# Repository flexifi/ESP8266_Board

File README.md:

# ESP8266_Board
A USB2Wifi test board to help working with and testing ESP8266 AT Commands.

(C)2015 Radu Motisan
http://www.pocketmagic.net/esp8266-troubleshooting

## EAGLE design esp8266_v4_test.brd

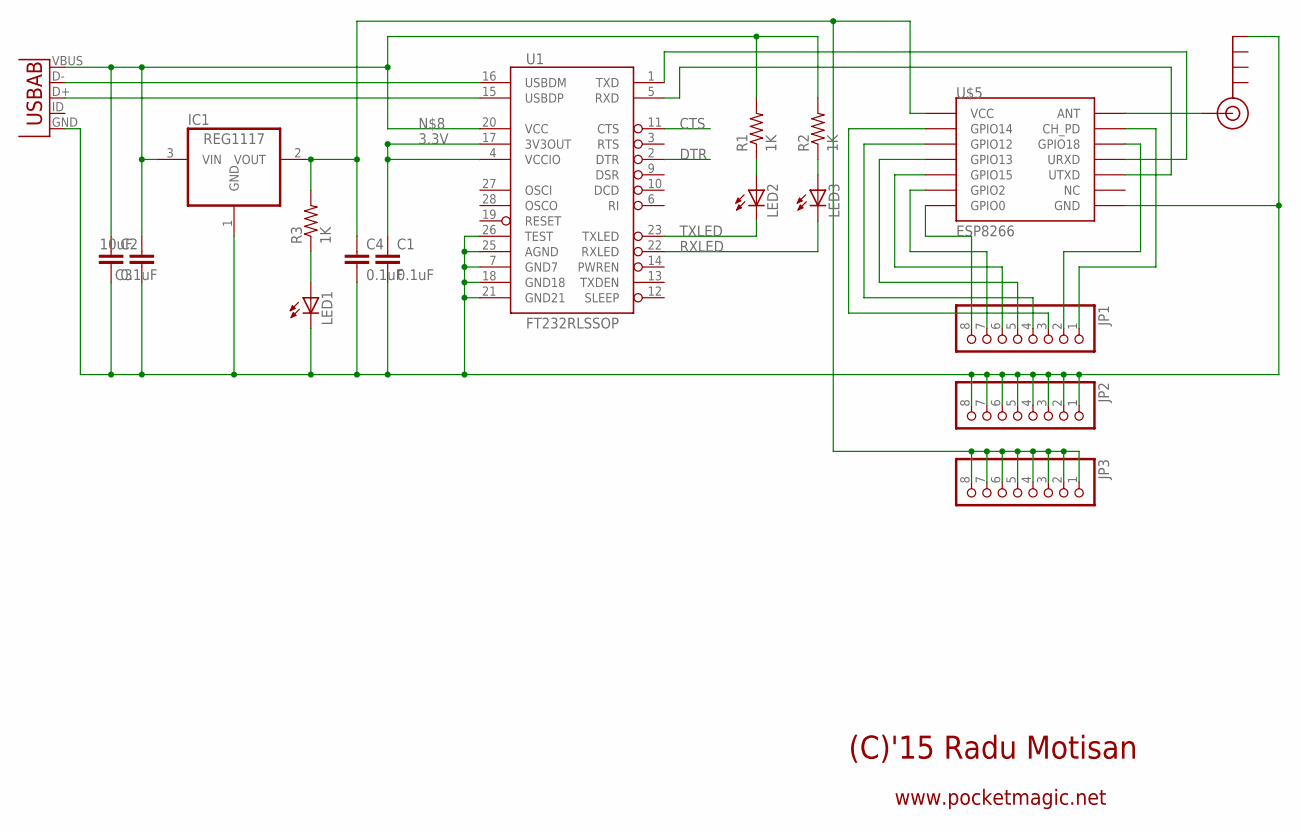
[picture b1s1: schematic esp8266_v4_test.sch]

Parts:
C1, C2, C4: 0.1uF; 0805
C3: 10uF; C0805K
IC1: REG1117; SOT223
J$1: SMA_EDGE; SMA-EDGE
JP1, JP2, JP3: PINHD-1X8CLEANBIG; 1X08-CLEANBIG
LED1, LED2, LED3: LEDCHIP-LED0805; CHIP-LED0805
R1, R2, R3: 1K; 0805
U1: FT232RLSSOP; SSOP28DB
U$2: USB_AB; USB-AB-MICRO-SMD
U$5: ESP8266; ESP-03

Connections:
3.3V: C1.1, U1.4 (VCCIO), U1.17 (3V3OUT)
CTS: U1.11 (CTS)
DTR: U1.2 (DTR)
unnamed: LED2.A, R1.1
unnamed: LED3.A, R2.1
unnamed: U1.16 (USBDM), U$2.D-
unnamed: U1.15 (USBDP), U$2.D+
unnamed: C4.1, IC1.2 (VOUT), JP3.1, JP3.2, JP3.3, JP3.4, JP3.5, JP3.6, JP3.7, JP3.8, R3.2, U$5.VCC
unnamed: J$1.SIG (SIGNAL), U$5.ANT
unnamed: JP1.1, U$5.CH_PD
unnamed: C2.1, C3.2, IC1.3 (VIN), R1.2, R2.2, U1.20 (VCC), U$2.VBUS
unnamed: U1.1 (TXD), U$5.URXD
unnamed: U1.5 (RXD), U$5.UTXD
unnamed: JP1.2, U$5.GPIO18
unnamed: JP1.8, U$5.GPIO0
unnamed: JP1.7, U$5.GPIO2
unnamed: JP1.6, U$5.GPIO15
unnamed: JP1.5, U$5.GPIO13
unnamed: JP1.4, U$5.GPIO12
unnamed: JP1.3, U$5.GPIO14
unnamed: LED1.A, R3.1
N$GND: C1.2, C2.2, C3.1, C4.2, IC1.1 (GND), J$1.GND@3 (GND), JP2.1, JP2.2, JP2.3, JP2.4, JP2.5, JP2.6, JP2.7, JP2.8, LED1.C, U1.7 (GND7), U1.18 (GND18), U1.21 (GND21), U1.25 (AGND), U1.26 (TEST), U$2.GND, U$5.GND
RXLED: LED3.C, U1.22 (RXLED)
TXLED: LED2.C, U1.23 (TXLED)

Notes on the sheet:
(C)'15 Radu Motisan
www.pocketmagic.net

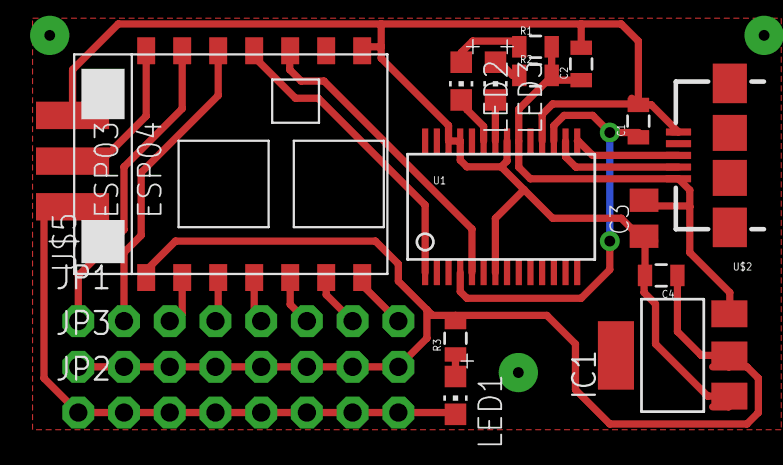
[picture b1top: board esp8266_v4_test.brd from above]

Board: 2 copper layers, 18 parts (0 on the bottom side), 22 nets.

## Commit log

2015-07-29 first release

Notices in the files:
parts and their libraries:
sparkfun-connectors: Licensing: CC v3.0 Share-Alike You are welcome to use this library for commercial purposes.
